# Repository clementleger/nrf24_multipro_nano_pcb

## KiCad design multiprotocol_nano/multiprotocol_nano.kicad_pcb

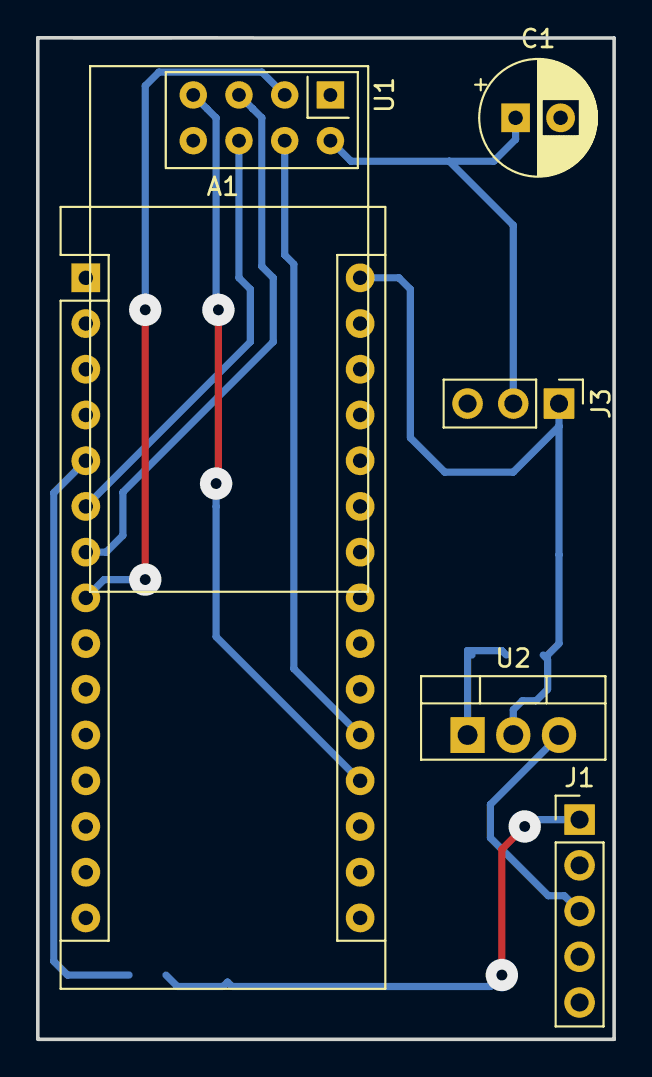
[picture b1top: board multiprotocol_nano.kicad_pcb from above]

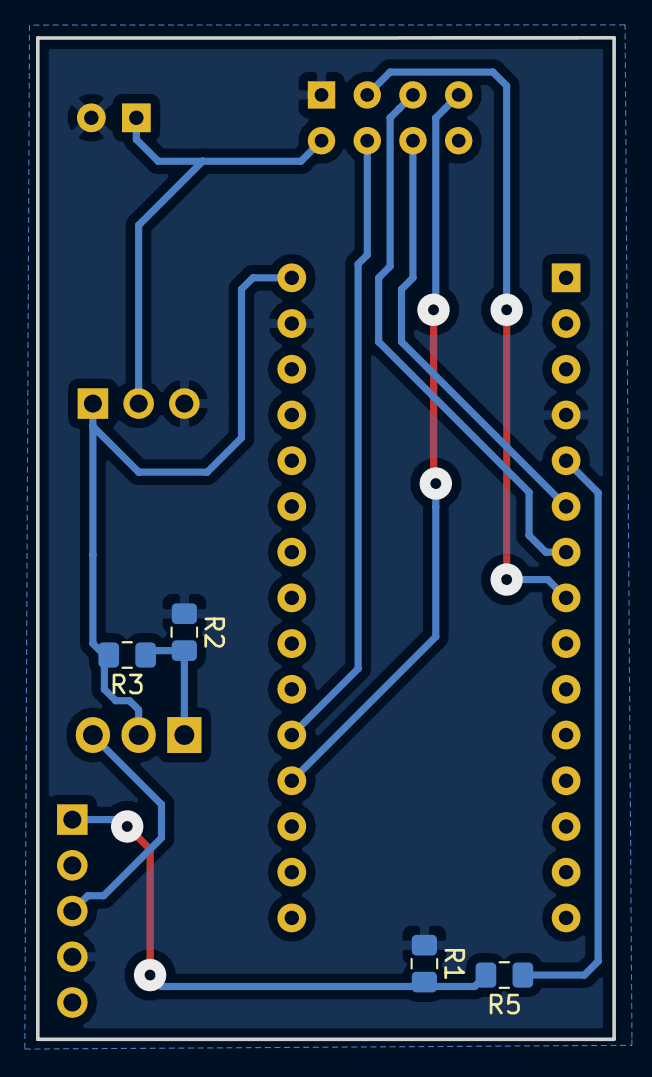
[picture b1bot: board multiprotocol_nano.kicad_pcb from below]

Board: 2 copper layers, 32.0 x 55.6 mm, 10 parts (4 on the bottom side), 12 nets.

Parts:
A1: Arduino_Nano_v3.x; Arduino_Nano
C1: CP; CP_Radial_D6.3mm_P2.50mm
J1: Conn_01x05; PinHeader_1x05_P2.54mm_Vertical
J3: Conn_01x03; PinHeader_1x03_P2.54mm_Vertical
R1, R5: 10K; R_0805_2012Metric_Pad1.15x1.40mm_HandSolder
R2: 1.2K; R_0805_2012Metric_Pad1.15x1.40mm_HandSolder
R3: 240; R_0805_2012Metric_Pad1.15x1.40mm_HandSolder
U1: NRF24L01_Breakout; nRF24L01_Breakout
U2: LM317_3PinPackage; TO-220-3_Vertical

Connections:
+3V3: C1.1, J3.2, U1.2
+BATT: J1.3, U2.3
GND: A1.4, A1.29, C1.2, J1.4, J3.3, R1.1, R2.1, U1.1
MISO: A1.19, U1.7
MOSI: A1.6, U1.6
NRF_CE: A1.8, U1.3
NRF_CS: A1.20, U1.4
unnamed: R2.2, R3.1, U2.1
PPM: J1.1, R1.2, R5.2
PPM_IN: A1.5, R5.1
SCLK: A1.7, U1.5
VCC: A1.30, J3.1, R3.2, U2.2

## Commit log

2018-08-02 PCB: inital commit with routed module
2018-09-01 Fix wrong package for LM317
